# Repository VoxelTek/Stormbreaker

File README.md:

# Stormbreaker
### ~~A ripoff of YveltalGriffin's Mjolnir~~ 
### A companion board for [Thundervolt](https://github.com/mackieks/thundervolt)

## What is this?
Stormbreaker is a multifunction circuit board intended to be used alongside [Thundervolt](https://github.com/mackieks/thundervolt) in Wii portables. It handles battery charging and monitoring, power switching, storage interfacing, and a bit more. See the full list of features here.

## Why did I design this?
Thundervolt, while incredible, does not provide any battery management capability, nor does it provide any way for a user to toggle power to the system outside of disconnecting power from Thundervolt itself. As such, following the completion of Thundervolt, its creator YveltalGriffin began work on a companion board, named "Mjolnir". Mjolnir would handle everything from battery management to storage to fan control and more, and would integrate seamlessly with Thundervolt. However, development on Mjolnir has been temporarily halted, which pushed me to make a companion board myself. Hence, Stormbreaker was born.

## Where did the name come from?
In Norse mythology, Thor is the God of Thunder, and is often seen alongside his hammer, Mjolnir. In the Marvel Cinematic Universe, Thor lost Mjolnir, and instead forged an axe called Stormbreaker. 

As such, it seemed fitting to name this board, born from the absense of Mjolnir, "Stormbreaker".
###### Disclaimer: this board is not capable of summoning the Bifrost. PRs are welcome.

## What can this board do?
Functionality is largely split between the 4 ICs.
#### U1 - BQ25895
- Battery charging
  - Fast charging capability
  - Play-and-charge capability
- Battery voltage monitoring
  - Used to determine approximate remaining battery capacity (i.e. "percent")
- Shipping mode
#### U2 - GL835
- microSD to USB 2.0 adapter
- Supports hot-swaping microSD cards
#### U3 - ATtiny1616
- Initialises ICs
- Monitors system
  - Shuts off console in event of over-temp
  - Engages shipping mode when requested
  - Responds to errors from U1
- Powers on/off console after button press
  - Has safe shutdown capability
- Drives Neopixel LED (WS2812 or compatible)
- Controls fan speed using PWM
- Communicates with Wii over I2C
  - RVLoader fork allows various adjustments, including charge currents and charge voltage
#### U4 - HUSB238A
- PD sink controller
- Uses USB-C PD to request higher voltages (up to 12V) to allow for faster charging with lower current draw

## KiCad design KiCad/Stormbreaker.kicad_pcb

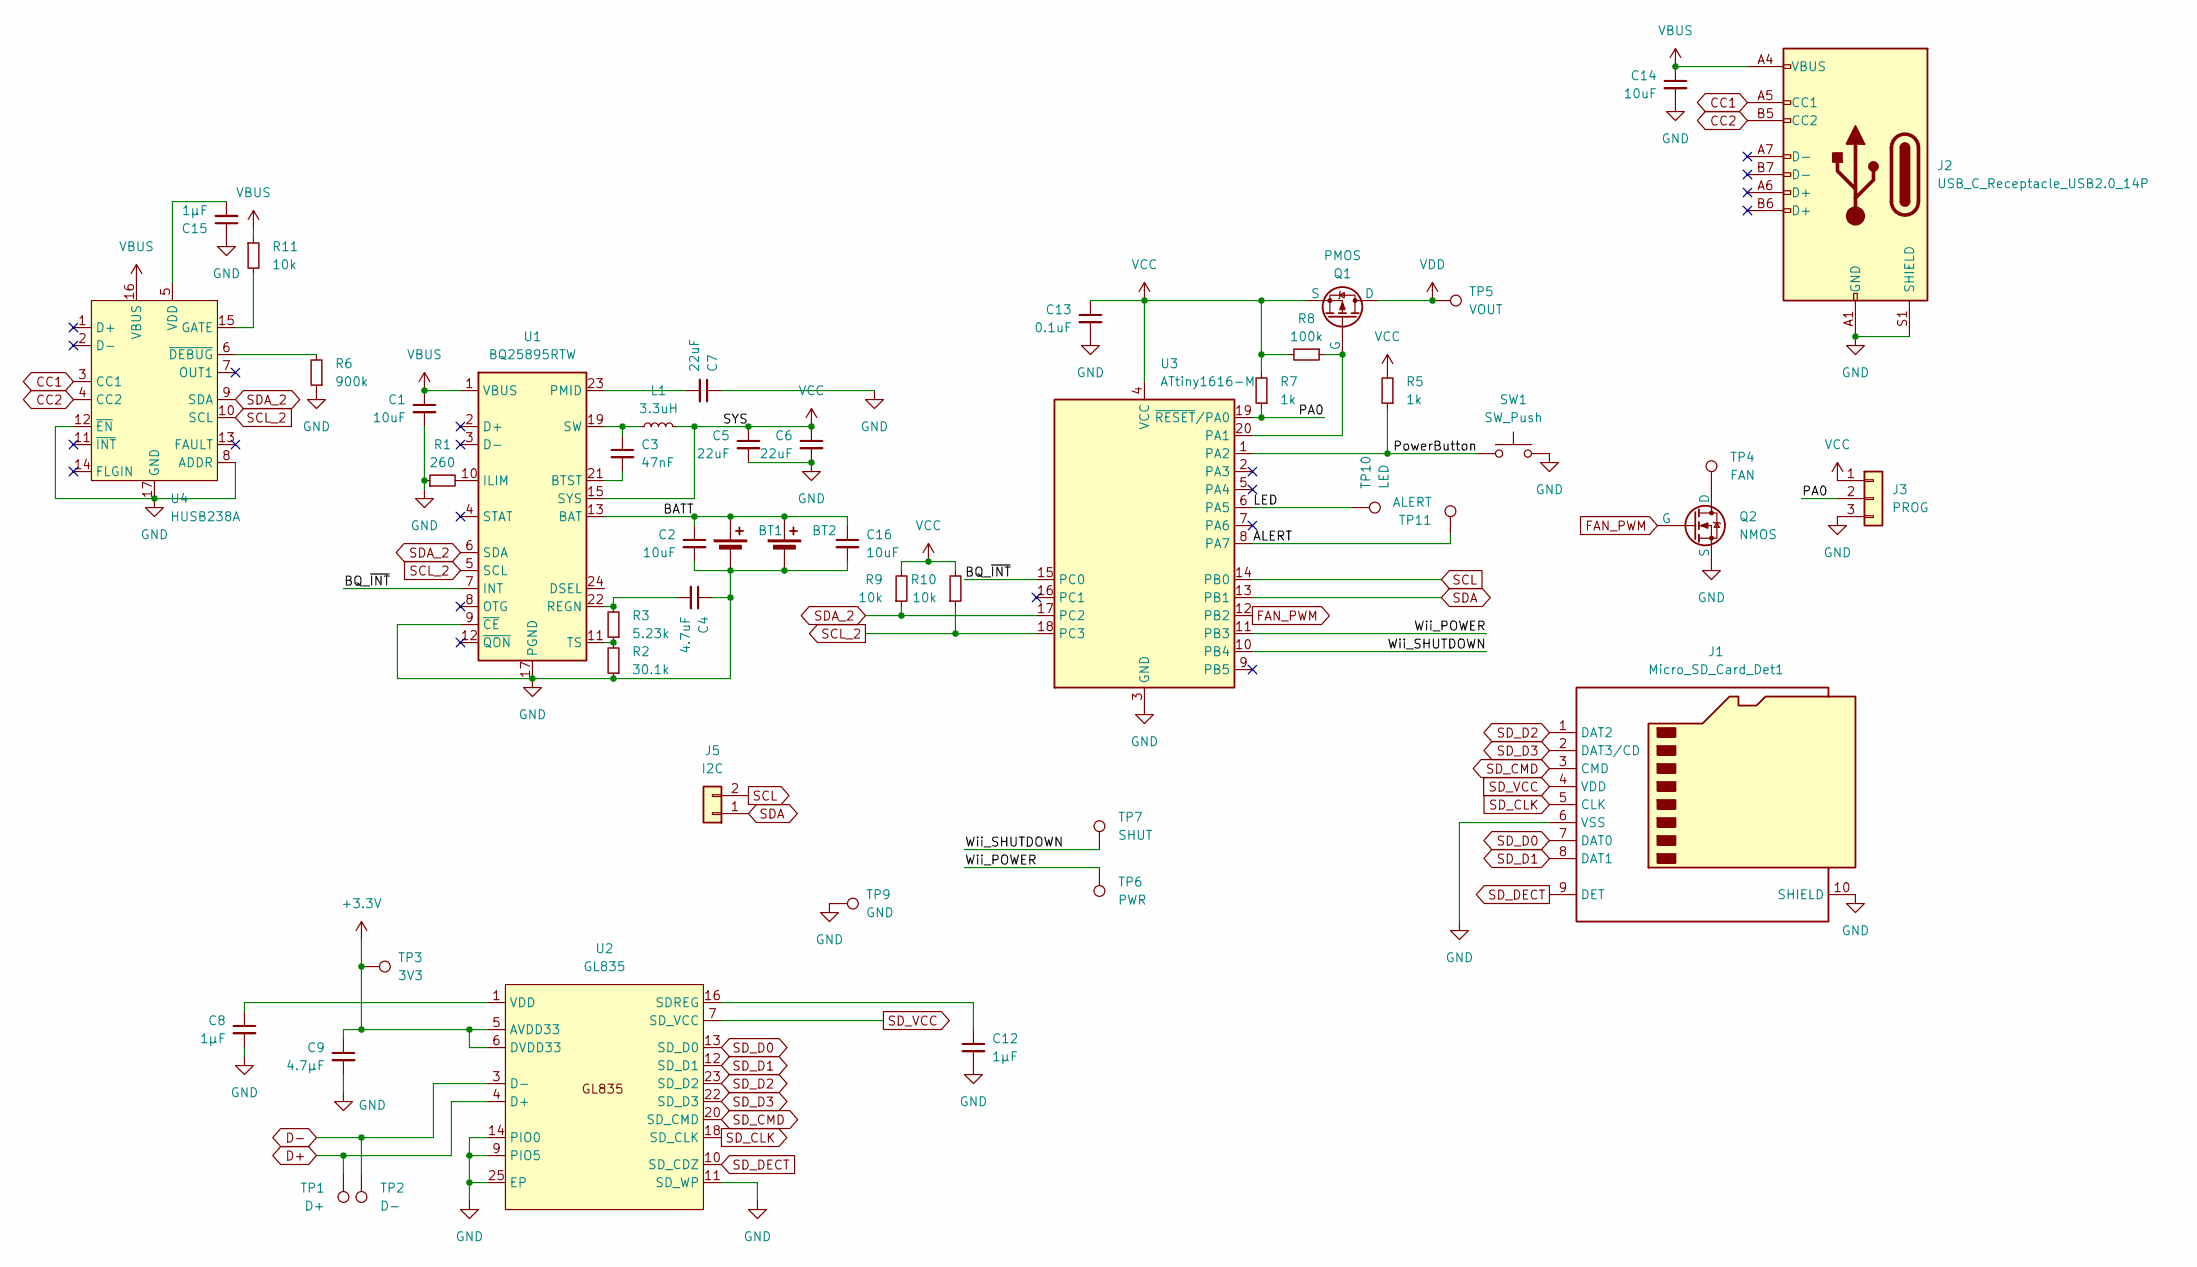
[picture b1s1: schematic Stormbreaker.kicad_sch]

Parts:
BT1: Battery_Cell; PinSocket_1x02_P1.27mm_Vertical
BT2: Battery_Cell; JST_PH_B2B-PH-K_1x02_P2.00mm_Vertical
C1, C2, C14, C16: 10uF; C_0603_1608Metric
C3: 47nF; C_0402_1005Metric
C4: 4.7uF; C_0402_1005Metric
C5, C6, C7: 22uF; C_0402_1005Metric
C8, C12, C15: 1μF; C_0402_1005Metric
C9: 4.7μF; C_0402_1005Metric
C13: 0.1uF; C_0603_1608Metric
J1: Micro_SD_Card_Det1; microSD_HC_Hirose_DM3D-SF
J2: USB_C_Receptacle_USB2.0_14P; USB_C_Receptacle_GCT_USB4105-xx-A_16P_TopMnt_Horizontal
J3: PROG; UPDI Pads
J5: I2C; PinSocket_1x02_P1.00mm_Vertical
L1: 3.3uH; L_PCMB053T
Q1: PMOS; Vishay_PowerPAK_1212-8_Single; Mouser au.mouser.com/ProductDetail/Vishay-Semi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
Q2: NMOS; SOT-523
R1: 260; R_0402_1005Metric
R2: 30.1k; R_0402_1005Metric
R3: 5.23k; R_0402_1005Metric
R5, R7: 1k; R_0402_1005Metric
R6: 900k; R_0402_1005Metric
R8: 100k; R_0402_1005Metric
R9, R10, R11: 10k; R_0402_1005Metric
SW1: SW_Push; SW_TL3330AF260QG
TP1: D+; TestPoint_Pad_D1.0mm_Small
TP2: D-; TestPoint_Pad_D1.0mm_Small
TP3: 3V3; TestPoint_Pad_D1.5mm
TP4: FAN; TestPoint_Pad_D1.0mm_Small
TP5: VOUT; TestPoint_Pad_D2.5mm
TP6: PWR; TestPoint_Pad_D1.0mm_Small
TP7: SHUT; TestPoint_Pad_D1.0mm_Small
TP9: GND; TestPoint_Pad_D2.5mm
TP10: LED; TestPoint_Pad_D1.0mm_Small
TP11: ALERT; TestPoint_Pad_D1.0mm_Small
U1: BQ25895RTW; Texas_RTW_WQFN-24-1EP_4x4mm_P0.5mm_EP2.7x2.7mm_ThermalVias
U2: GL835; HVQFN-24-1EP_4x4mm_P0.5mm_EP2.5x2.5mm
U3: ATtiny1616-M; VQFN-20-1EP_3x3mm_P0.4mm_EP1.7x1.7mm
U4: HUSB238A; QFN-16-1EP_3x3mm_P0.5mm_EP1.7x1.7mm_ThermalVias

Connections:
+3.3V: C9.1, TP3.1, U2.5 (AVDD33), U2.6 (DVDD33)
/ALERT: TP11.1, U3.8 (PA7)
/BATT: BT1.1 (+), BT2.1 (+), C2.1, C16.1, U1.13 (BAT), U1.14 (BAT)
/BQ_~INT: U1.7 (INT), U3.15 (PC0)
/LED: TP10.1, U3.6 (PA5)
/PA0: J3.2, R7.1, U3.19 (~RESET/PA0)
/PowerButton: R5.1, SW1.1, U3.1 (PA2)
/Wii_POWER: TP6.1, U3.11 (PB3)
/Wii_SHUTDOWN: TP7.1, U3.10 (PB4)
CC1: J2.A5 (CC1), U4.3 (CC1)
CC2: J2.B5 (CC2), U4.4 (CC2)
D+: TP1.1, U2.4 (D+)
D-: TP2.1, U2.3 (D-)
FAN_PWM: Q2.1 (G), U3.12 (PB2)
GND: BT1.2 (-), BT2.2 (-), C1.2, C2.2, C4.1, C5.2, C6.2, C7.1, C8.2, C9.2, C12.2, C13.2, C14.2, C15.1, C16.2, J1.6 (VSS), J1.10 (SHIELD), J1.11 (SHIELD), J2.A1 (GND), J2.A12 (GND), J2.B1 (GND), J2.B12 (GND), J2.S1 (SHIELD), J3.3, Q2.2 (S), R1.1, R2.1, R6.1, SW1.2, SW1.MP, TP9.1, U1.9 (~CE), U1.17 (PGND), U1.18 (PGND), U1.25 (PGND), U2.9 (PIO5), U2.11 (SD_WP), U2.14 (PIO0), U2.25 (EP), U3.3 (GND), U3.21 (GND), U4.8 (ADDR), U4.12 (~EN), U4.17 (GND)
unnamed: C3.1, L1.1, U1.19 (SW), U1.20 (SW)
unnamed: Q1.4 (G), R8.1, U3.20 (PA1)
unnamed: Q2.3 (D), TP4.1
unnamed: C3.2, U1.21 (BTST)
unnamed: R1.2, U1.10 (ILIM)
unnamed: C7.2, U1.23 (PMID)
unnamed: C4.2, R3.2, U1.22 (REGN)
unnamed: R2.2, R3.1, U1.11 (TS)
unnamed: C12.1, U2.16 (SDREG)
unnamed: C8.1, U2.1 (VDD)
unnamed: R11.2, U4.15 (GATE)
unnamed: C15.2, U4.5 (VDD)
unnamed: R6.2, U4.6 (~DEBUG)
SCL: J5.2, U3.14 (PB0)
SCL_2: R10.1, U1.5 (SCL), U3.18 (PC3), U4.10 (SCL)
SDA: J5.1, U3.13 (PB1)
SDA_2: R9.1, U1.6 (SDA), U3.17 (PC2), U4.9 (SDA)
SD_CLK: J1.5 (CLK), U2.18 (SD_CLK)
SD_CMD: J1.3 (CMD), U2.20 (SD_CMD)
SD_D0: J1.7 (DAT0), U2.13 (SD_D0)
SD_D1: J1.8 (DAT1), U2.12 (SD_D1)
SD_D2: J1.1 (DAT2), U2.23 (SD_D2)
SD_D3: J1.2 (DAT3/CD), U2.22 (SD_D3)
SD_DECT: J1.9 (DET), U2.10 (SD_CDZ)
SD_VCC: J1.4 (VDD), U2.7 (SD_VCC)
VBUS: C1.1, C14.1, J2.A4 (VBUS), J2.A9 (VBUS), J2.B4 (VBUS), J2.B9 (VBUS), R11.1, U1.1 (VBUS), U4.16 (VBUS)
VCC: C5.1, C6.1, C13.1, J3.1, L1.2, Q1.1 (S), Q1.2 (S), Q1.3 (S), R5.2, R7.2, R8.2, R9.2, R10.2, U1.15 (SYS), U1.16 (SYS), U3.4 (VCC); also elsewhere on the board
VDD: Q1.5 (D), TP5.1

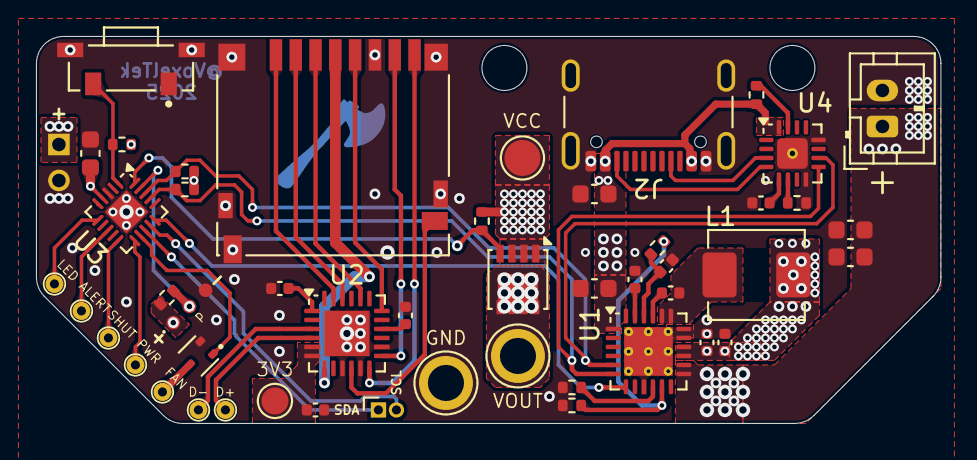
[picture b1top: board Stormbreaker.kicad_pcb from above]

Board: 4 copper layers, 50.2 x 21.5 mm, 49 parts (0 on the bottom side), 43 nets.

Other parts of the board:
TP8: VCC; TestPoint_Pad_D2.0mm

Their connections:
VCC: TP8.1; also elsewhere on the board

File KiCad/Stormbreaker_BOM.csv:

Id;Designator;Footprint;Quantity;Designation;Supplier and ref
3;C13;C_0603_1608Metric;1;0.1uF;
5;C5,C7,C6;C_0402_1005Metric;3;22uF;
6;U1;Texas_RTW_WQFN-24-1EP_4x4mm_P0.5mm_EP2.7x2.7mm_ThermalVias;1;BQ25895RTW;
7;R9,R10,R11;R_0402_1005Metric;3;10k;
8;U3;VQFN-20-1EP_3x3mm_P0.4mm_EP1.7x1.7mm;1;ATtiny1616-M;
9;C4,C9;C_0402_1005Metric;2;4.7uF;
11;L1;L_PCMB053T;1;3.3uH;
15;C12,C15,C8;C_0402_1005Metric;3;1μF;
16;R1;R_0402_1005Metric;1;260;
17;U2;HVQFN-24-1EP_4x4mm_P0.5mm_EP2.5x2.5mm;1;~;
18;C2,C1,C14,C16;C_0603_1608Metric;4;10uF;
20;J2;USB_C_Receptacle_GCT_USB4105-xx-A_16P_TopMnt_Horizontal;1;USB_C_Receptacle_USB2.0_14P;
21;BT2;JST_PH_B2B-PH-K_1x02_P2.00mm_Vertical;1;Battery_Cell;
23;Q2;SOT-523;1;NMOS;
24;Q1;Vishay_PowerPAK_1212-8_Single;1;PMOS;
25;J1;microSD_HC_Hirose_DM3D-SF;1;Micro_SD_Card_Det1;
28;SW1;SW_TL3330AF260QG;1;SW_Push;
29;R2;R_0402_1005Metric;1;30.1k;
30;R7,R5;R_0402_1005Metric;2;1k;
32;R6;R_0402_1005Metric;1;900k;
34;R8;R_0402_1005Metric;1;100k;
36;R3;R_0402_1005Metric;1;5.23k;
37;U4;QFN-16-1EP_3x3mm_P0.5mm_EP1.7x1.7mm_ThermalVias;1;HUSB238A;
39;C3;C_0402_1005Metric;1;47nF;

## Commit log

2025-05-22 Switch to larger inductor
2025-08-15 Switch to different button
    Something's up with KiCad, not sure why.
2025-08-28 WIP -- Move to PlatformIO
2025-08-28 Rename `main.cpp` to `main.c`
2025-08-29 More code stuff
2025-09-01 more software work
2025-09-02 Nearing completion of firmware rewrite
2025-09-04 Nearing completion
2025-09-04 Add ADC functions, PWM fan control to come
2025-09-04 Minor cleanups
2025-09-04 Update bq25895
2025-09-04 Several misc PCB improvements
2025-09-07 Fix I2C communication between RVLoader and Storm
2025-09-07 Whitespace cleanup
2025-09-08 Remove original `.ino`, implement fan PWM, misc
2025-10-06 Misc board improvements
2025-10-07 v3 hardware design: largely complete
2025-10-07 Rework of some things
    TODO:
    - Fix I2C functions
    - Add HUSB238A setup code
2025-10-07 Improve and simplify I2C code
2025-10-08 Nearing completion of revision 3
2025-10-08 Add fancy logo
2025-10-08 Misc changes, README.md update
2025-10-09 Minor hardware changes
2025-10-09 Update README.md
    Replace image, slight text changes and additions
2025-10-09 Minor misc code changes
2025-10-09 Update README.md
    Replace main image, add animated GIF of spinning board
2025-10-10 Fix 3D model, other misc changes
2025-10-10 Update platformio-build.yml
    Add submodules, hopefully
2025-10-10 Update platformio-build.yml
    Fix submodules again, hopefully
2025-10-12 Fix division
2025-10-13 Temporarily remove RVLoader dir
2025-10-13 Add RVLoader submodule
2025-10-13 Add status badges to README.md
2025-10-13 Update RVLoader
2025-12-27 Minor changes, regenerate gerbers
2026-01-08 Add alternate microSD slot
2026-01-08 Edit BOM, compress gerbers, fix doxygen
2026-01-08 Generate ibom, add value for GL835
